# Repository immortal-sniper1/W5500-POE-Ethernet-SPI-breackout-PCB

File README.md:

# W5500-POE-Ethernet-SPI-breackout-PCB

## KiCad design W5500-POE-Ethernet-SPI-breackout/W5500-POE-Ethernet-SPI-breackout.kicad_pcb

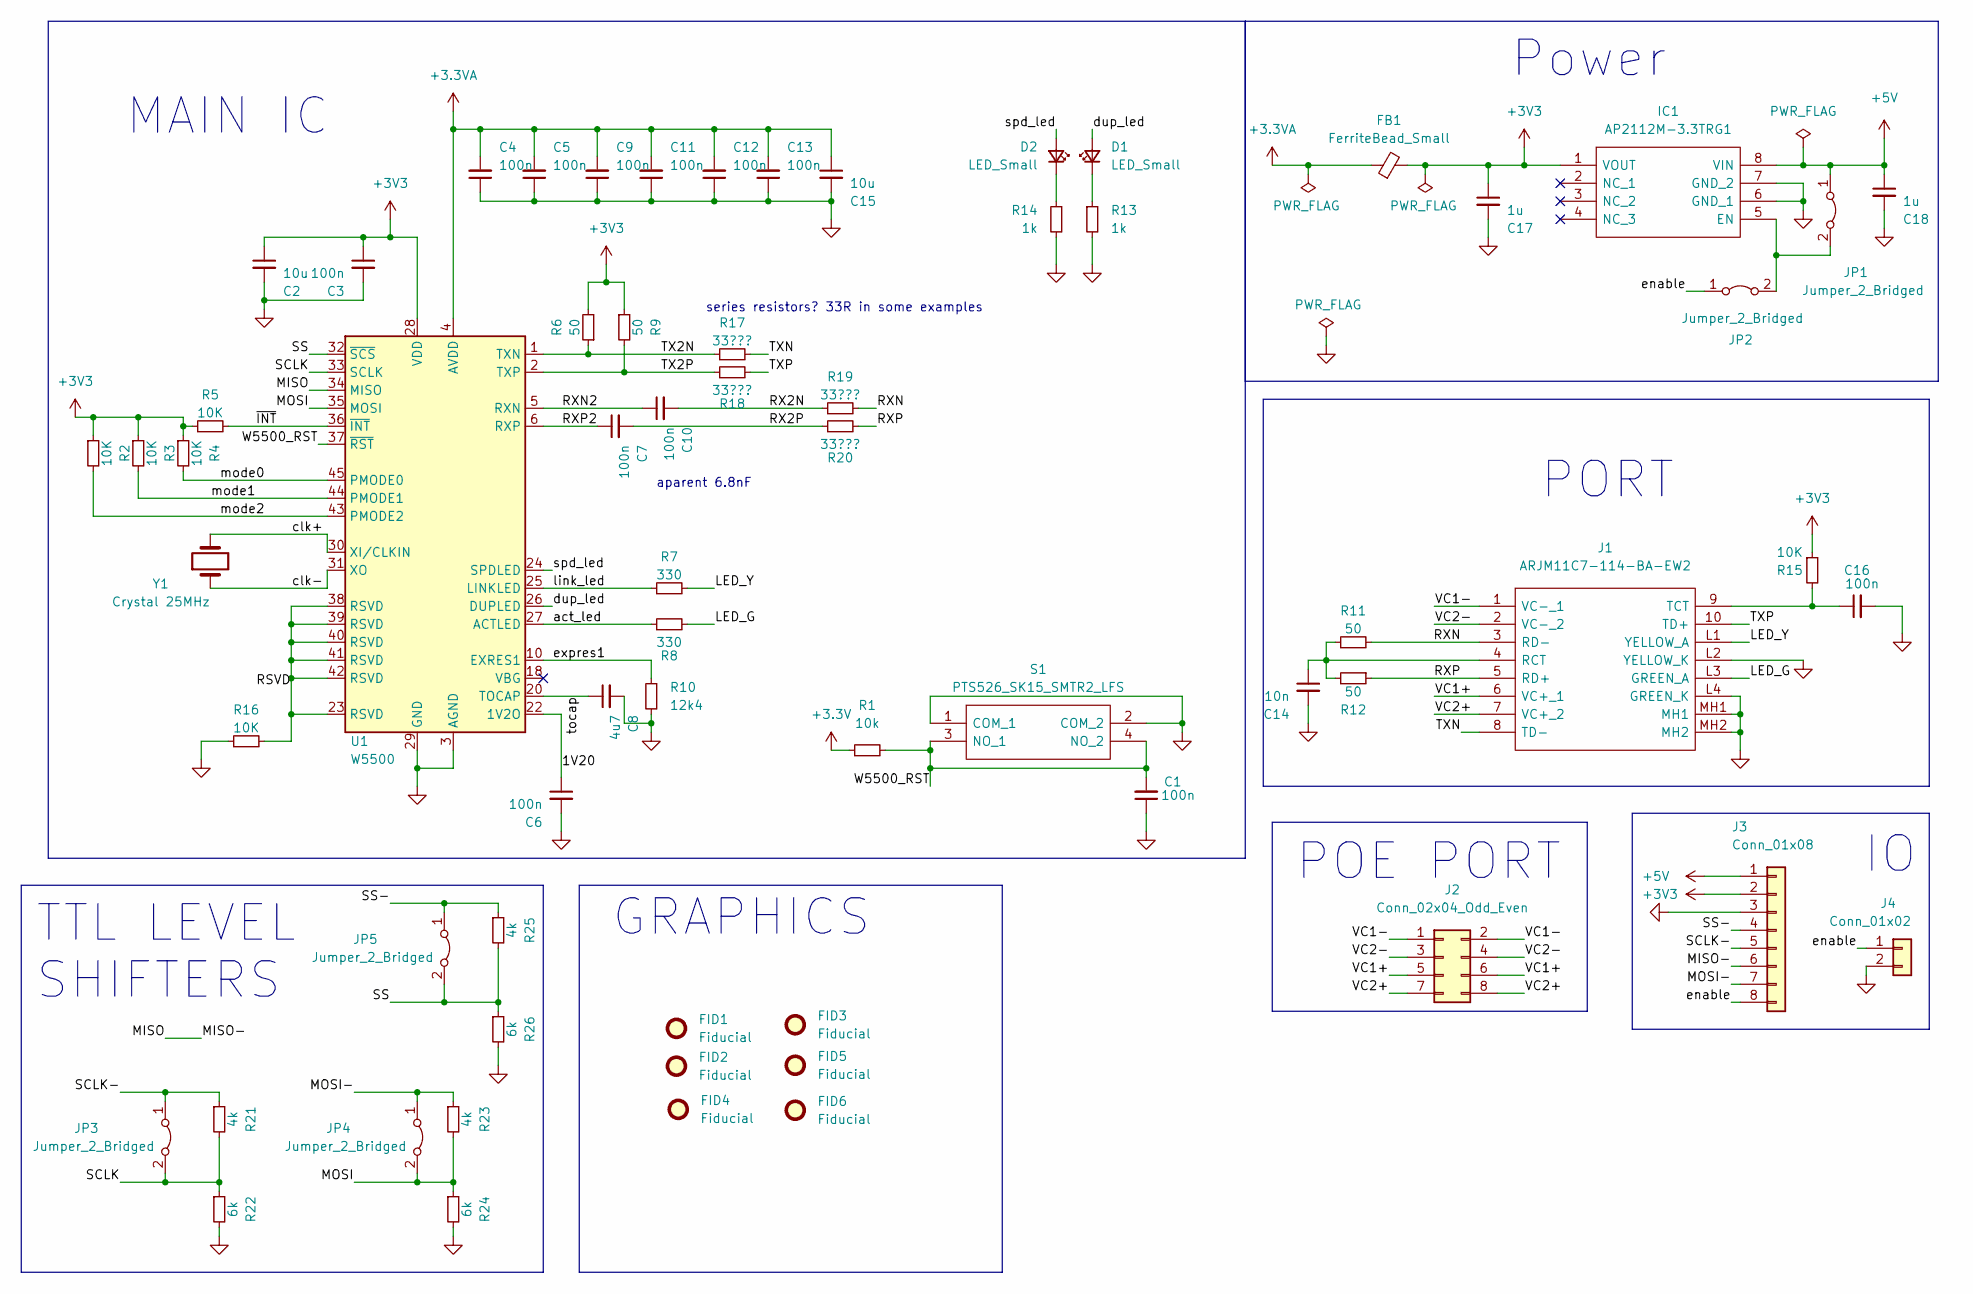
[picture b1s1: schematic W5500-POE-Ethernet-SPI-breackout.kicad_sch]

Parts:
C1, C3, C4, C5, C6, C7, C9, C10, C11, C12, C13, C16: 100n; C_0805_2012Metric
C2, C15: 10u; C_0805_2012Metric
C8: 4u7; C_0805_2012Metric
C14: 10n; C_0805_2012Metric
C17, C18: 1u; C_0805_2012Metric
D1, D2: LED_Small; LED_0603_1608Metric_Pad1.05x0.95mm_HandSolder
FB1: FerriteBead_Small; R_0402_1005Metric_Pad0.72x0.64mm_HandSolder
FID1, FID2: Fiducial; Fiducial_0.5mm_Mask1mm
FID3: Fiducial; KiCad-Logo2_12mm_SilkScreen
FID4: Fiducial; OSHW-LOGO-L
FID5: Fiducial; ESD-Logo_8.9x8mm_SilkScreen
FID6: Fiducial; WEEE-Logo_5.6x8mm_SilkScreen
IC1: AP2112M-3.3TRG1; SOIC127P600X170-8N; Mouser Part Number 621-AP2112M-3.3TRG1
J1: ARJM11C7-114-BA-EW2; ARJM11C7114BAEW2; Mouser Part Number 815-RJM11C7114BAEW2
J2: Conn_02x04_Odd_Even; PinSocket_2x04_P2.54mm_Vertical
J3: Conn_01x08; PinSocket_1x08_P2.54mm_Vertical
J4: Conn_01x02; PinSocket_1x02_P2.54mm_Vertical
JP1, JP2, JP3, JP4, JP5: Jumper_2_Bridged; SolderJumper-2_P1.3mm_Bridged_RoundedPad1.0x1.5mm
R1: 10k; R_0603_1608Metric_Pad0.98x0.95mm_HandSolder
R2, R3, R4, R5, R15, R16: 10K; R_0603_1608Metric_Pad0.98x0.95mm_HandSolder
R6, R9, R11, R12: 50; R_0603_1608Metric_Pad0.98x0.95mm_HandSolder
R7, R8: 330; R_0603_1608Metric_Pad0.98x0.95mm_HandSolder
R10: 12k4; R_Axial_DIN0207_L6.3mm_D2.5mm_P5.08mm_Vertical
R13, R14: 1k; R_0603_1608Metric_Pad0.98x0.95mm_HandSolder
R17, R18, R19, R20: 33???; R_0603_1608Metric_Pad0.98x0.95mm_HandSolder
R21, R23, R25: 4k; R_0603_1608Metric_Pad0.98x0.95mm_HandSolder
R22, R24, R26: 6k; R_0603_1608Metric_Pad0.98x0.95mm_HandSolder
S1: PTS526_SK15_SMTR2_LFS; PTS526SK15SMTR2LFS; Mouser Part Number 611-PTS526SK15SMR2L
U1: W5500; LQFP-48_7x7mm_P0.5mm
Y1: Crystal 25MHz; ATS120SM

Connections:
+3.3VA: C4.2, C5.2, C9.2, C11.2, C12.2, C13.2, C15.1, FB1.1, U1.4 (AVDD), U1.8 (AVDD), U1.11 (AVDD), U1.15 (AVDD), U1.17 (AVDD), U1.21 (AVDD)
+5V: C18.1, IC1.8 (VIN), J3.1, JP1.1 (A)
/1V20: C6.1, U1.22 (1V2O)
/LED_G: J1.L3 (GREEN_A), R8.2
/LED_Y: J1.L1 (YELLOW_A), R7.2
/MISO: J3.6, U1.34 (MISO)
/MOSI: JP4.2 (B), R23.2, R24.1, U1.35 (MOSI)
/MOSI-: J3.7, JP4.1 (A), R23.1
/RSVD: R16.2, U1.23 (RSVD), U1.38 (RSVD), U1.39 (RSVD), U1.40 (RSVD), U1.41 (RSVD), U1.42 (RSVD)
/RX2N: C10.2, R19.1
/RX2P: C7.2, R20.1
/RXN: J1.3 (RD-), R11.2, R19.2
/RXN2: C10.1, U1.5 (RXN)
/RXP: J1.5 (RD+), R12.1, R20.2
/RXP2: C7.1, U1.6 (RXP)
/SCLK: JP3.2 (B), R21.2, R22.1, U1.33 (SCLK)
/SCLK-: J3.5, JP3.1 (A), R21.1
/SS: JP5.2 (B), R25.2, R26.1, U1.32 (~SCS)
/SS-: J3.4, JP5.1 (A), R25.1
/TX2N: R6.1, R17.1, U1.1 (TXN)
/TX2P: R9.2, R18.1, U1.2 (TXP)
/TXN: J1.8 (TD-), R17.2
/TXP: J1.10 (TD+), R18.2
/VC1+: J1.6 (VC+_1), J2.5, J2.6
/VC1-: J1.1 (VC-_1), J2.1, J2.2
/VC2+: J1.7 (VC+_2), J2.7, J2.8
/VC2-: J1.2 (VC-_2), J2.3, J2.4
/W5500_RST: C1.2, R1.2, S1.3 (NO_1), S1.4 (NO_2), U1.37 (~RST)
/act_led: R8.1, U1.27 (ACTLED)
/clk+: U1.30 (XI/CLKIN), Y1.2
/clk-: U1.31 (XO), Y1.1
/dup_led: D1.2 (A), U1.26 (DUPLED)
/enable: J3.8, J4.1, JP2.1 (A)
/expres1: R10.1, U1.10 (EXRES1)
/link_led: R7.1, U1.25 (LINKLED)
/mode0: R4.2, U1.45 (PMODE0)
/mode1: R3.2, U1.44 (PMODE1)
/mode2: R2.2, U1.43 (PMODE2)
/spd_led: D2.2 (A), U1.24 (SPDLED)
/tocap: C8.1, U1.20 (TOCAP)
/~INT: R5.2, U1.36 (~INT)
GND: C1.1, C2.2, C3.2, C4.1, C5.1, C6.2, C8.2, C9.1, C11.1, C12.1, C13.1, C14.2, C15.2, C16.2, C17.2, C18.2, IC1.6 (GND_1), IC1.7 (GND_2), J1.L2 (YELLOW_K), J1.L4 (GREEN_K), J1.MH1, J1.MH2, J3.3, J4.2, R10.2, R13.2, R14.2, R16.1, R22.2, R24.2, R26.2, S1.1 (COM_1), S1.2 (COM_2), U1.3 (AGND), U1.9 (AGND), U1.14 (AGND), U1.16 (AGND), U1.19 (AGND), U1.29 (GND), U1.48 (AGND)
unnamed: C14.1, J1.4 (RCT), R11.1, R12.2
unnamed: C16.1, J1.9 (TCT), R15.2
unnamed: D1.1 (K), R13.1
unnamed: D2.1 (K), R14.1
unnamed: IC1.5 (EN), JP1.2 (B), JP2.2 (B)

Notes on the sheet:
aparent 6.8nF
series resistors? 33R in some examples
PORT
Power
TTL LEVEL SHIFTERS
GRAPHICS
MAIN IC
POE PORT

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
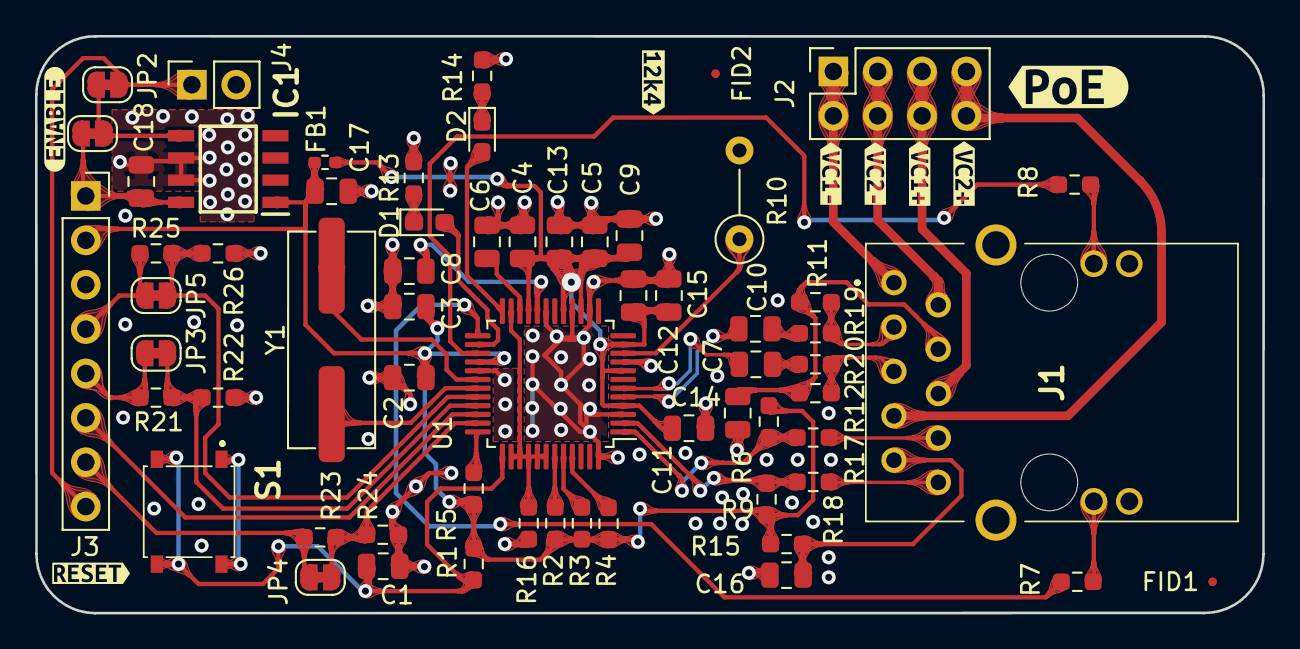
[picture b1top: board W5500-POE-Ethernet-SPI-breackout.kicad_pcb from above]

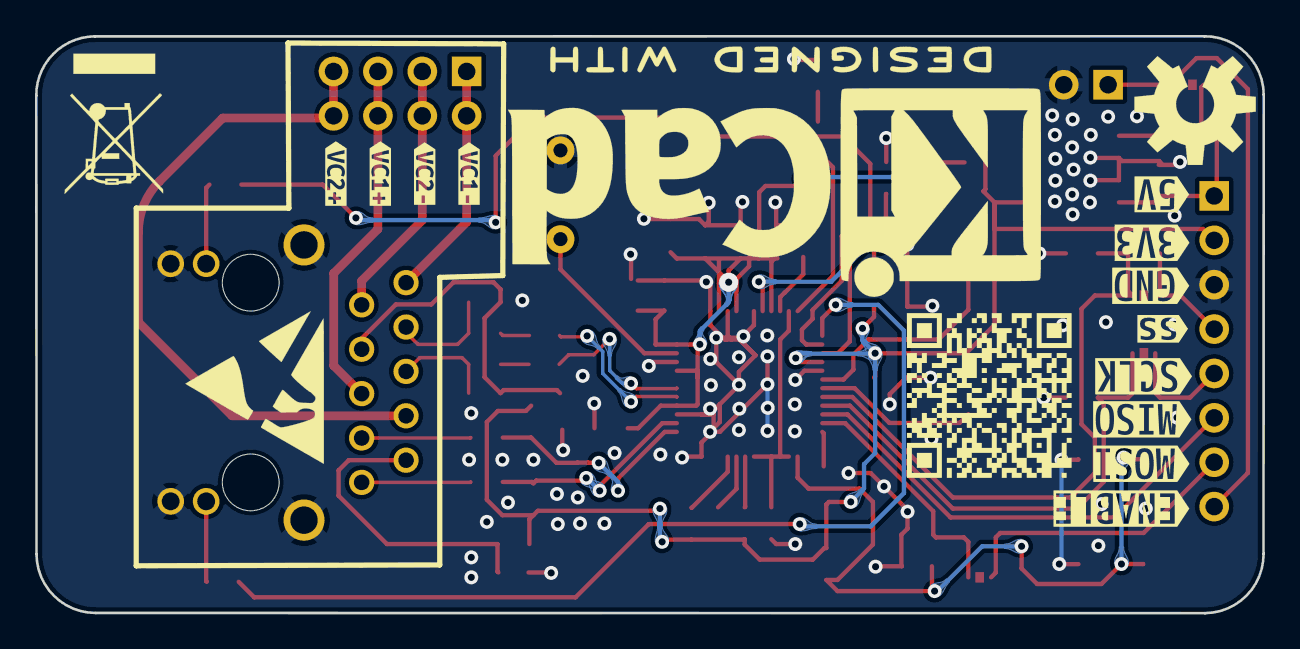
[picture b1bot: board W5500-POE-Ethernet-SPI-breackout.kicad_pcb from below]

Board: 2 copper layers, 70.3 x 33.0 mm, 87 parts (17 on the bottom side), 48 nets.

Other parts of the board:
 : LOGO
kibuzzard-627C18AA, kibuzzard-627C18AA#2: G***; kibuzzard-627C18AA
kibuzzard-627C18B6, kibuzzard-627C18B6#2: G***; kibuzzard-627C18B6
kibuzzard-627C18C3, kibuzzard-627C18C3#2: G***; kibuzzard-627C18C3
kibuzzard-627C18CA, kibuzzard-627C18CA#2: G***; kibuzzard-627C18CA
kibuzzard-627C225D: G***; kibuzzard-627C225D
kibuzzard-6280C015: G***; kibuzzard-6280C015
kibuzzard-62827A52: G***; kibuzzard-62827A52
kibuzzard-628279F4: G***; kibuzzard-628279F4
kibuzzard-6338560E: G***; kibuzzard-6338560E
kibuzzard-6338564E: G***; kibuzzard-6338564E
kibuzzard-6338565D: G***; kibuzzard-6338565D
kibuzzard-6338566D: G***; kibuzzard-6338566D
kibuzzard-6338567A: G***; kibuzzard-6338567A
kibuzzard-63385628: G***; kibuzzard-63385628
kibuzzard-63385636: G***; kibuzzard-63385636
kibuzzard-63385685: G***; kibuzzard-63385685
